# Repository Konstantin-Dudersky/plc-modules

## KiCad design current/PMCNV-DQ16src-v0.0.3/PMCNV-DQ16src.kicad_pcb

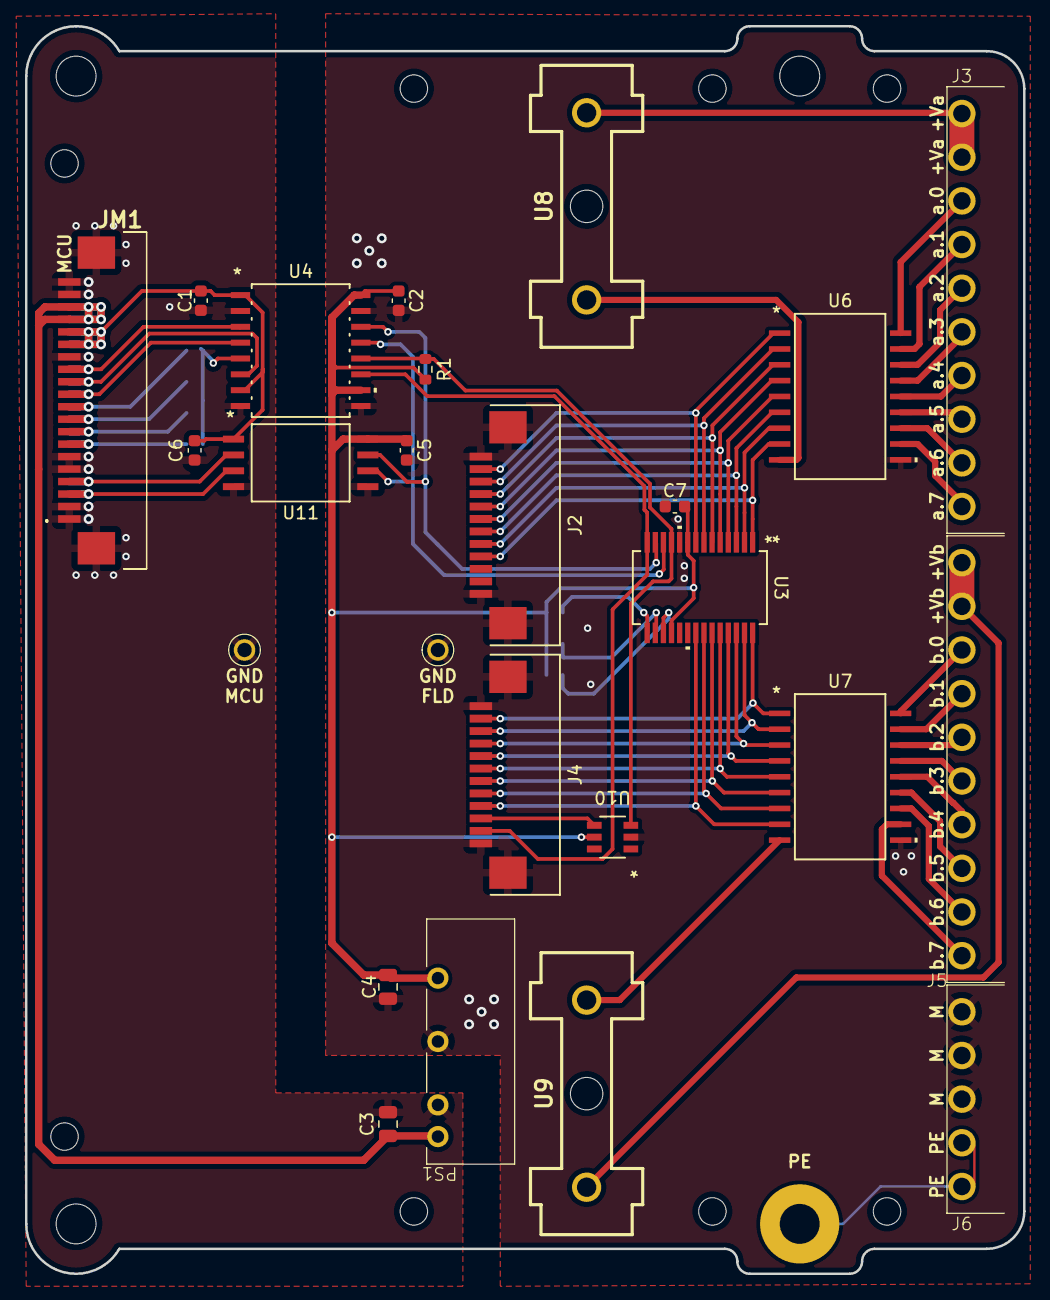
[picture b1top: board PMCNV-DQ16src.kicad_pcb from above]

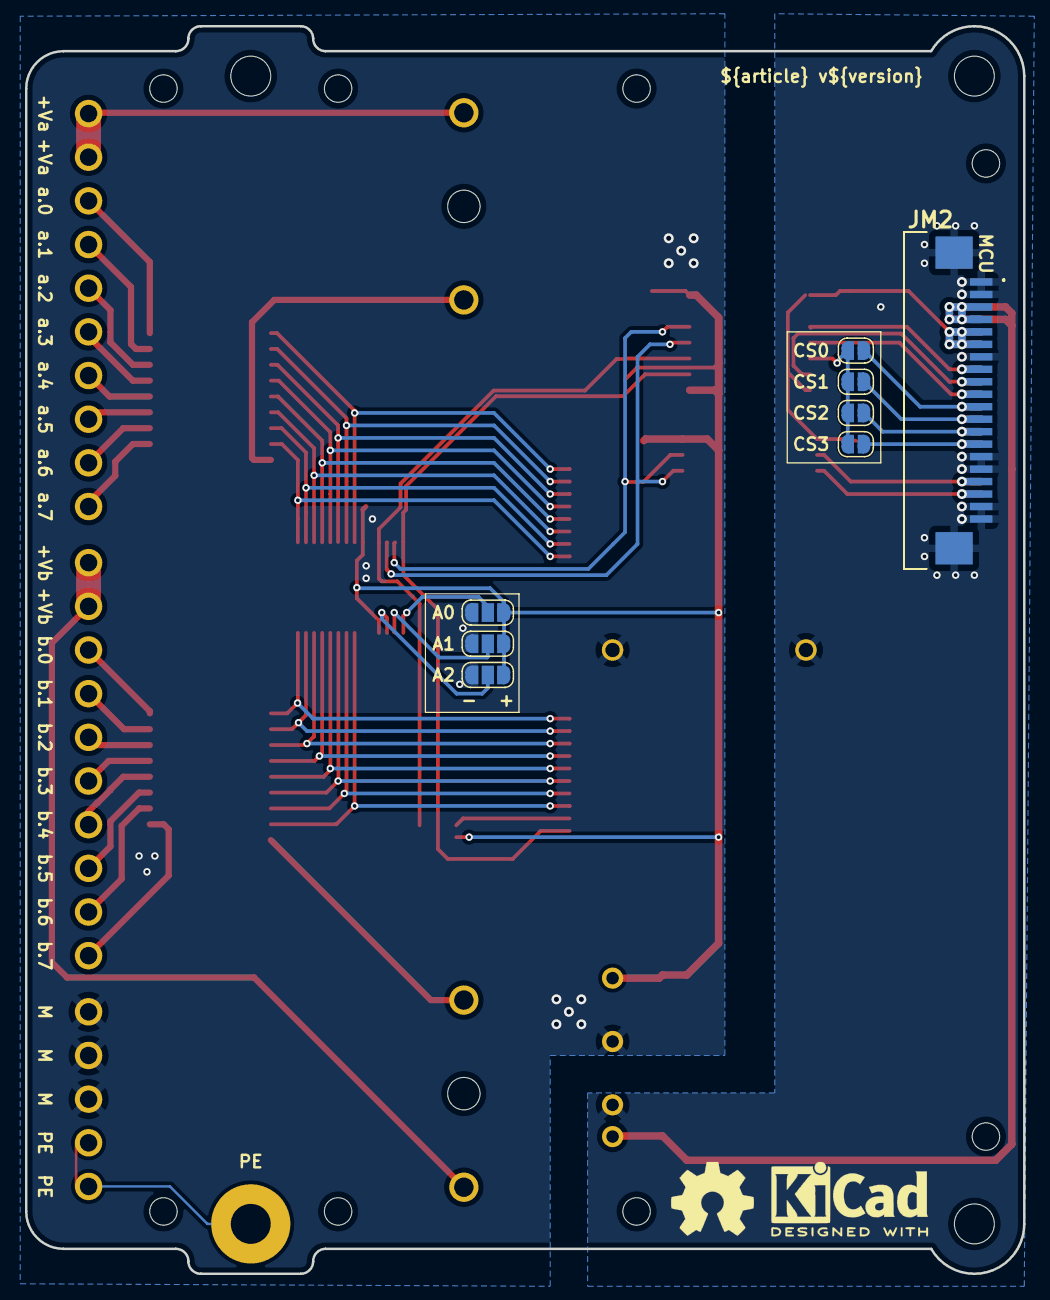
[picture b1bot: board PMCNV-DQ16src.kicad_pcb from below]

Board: 2 copper layers, 80.0 x 100.0 mm, 41 parts (10 on the bottom side), 60 nets.

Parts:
C1, C2, C5, C6, C7: 100nF; C_0603_1608Metric
C3: 4.7uF; C_0805_2012Metric
C4: 10uF; C_0805_2012Metric
H1, H2, H3: MountingHole_M3
J2, J4: AFA07-S12FCC-00; CONN10_AFA07-S12_JUS
J3, J5: 15EDGRC-3.5-10P
J6: 15EDGRC-3.5-05P
JM1, JM2: AFA07-S20FCC-00; AFA07S20FCA00
JP1, JP2, JP3, JP4: SolderJumper_2_Open; SolderJumper-2_P1.3mm_Open_RoundedPad1.0x1.5mm
JP5, JP6, JP7: SolderJumper_3_Open; SolderJumper-3_P1.3mm_Open_RoundedPad1.0x1.5mm
PE1: PE
PS1: 5V/5V; B2405LS-1WR3
R1: 10k; R_0603_1608Metric
SP1: PM_LED-xx-v0.0.1
U1: PM-ESP32C3_v0.0.5
U2, U5: 5117
U3: MCP23017_SS; SSOP28_MC_MCH
U4: CA-IS3741HW; SOIC16-WBW_CLG
U6, U7: TBD62783AFG; SOP18-P-375-1p27_TOS-M
U8, U9: 64900001039; 649-Series-Holder
U10: SN74LVC2G14DBVR; DBV6-M
U11: CA-IS3021G; SOICW8_CLG
kicad_logo: KiCad-Logo2_5mm_SilkScreen
oshw_logo: OSHW-Symbol_6.7x6mm_SilkScreen

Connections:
+3.3V_MCU: C1.1, C6.1, JM1.15 (Pin_11), JM1.16 (Pin_11), JM2.5, JM2.6, U4.1 (VDD), U4.7 (ENA), U11.1 (VDDa)
+5V_CNV: C2.1, C4.1, C5.1, C7.1, JP5.3 (B), JP6.3 (B), JP7.3 (B), PS1.6 (+V), R1.1, U3.9 (VDD), U3.18 (~RESET), U4.10 (ENB), U4.16 (VISO), U10.5 (VCC), U11.8 (VDDb)
+5V_MCU: C3.1, JM1.17 (Pin_11), JM1.18 (Pin_11), JM2.3, JM2.4, PS1.1 (Vin)
+V_a: J3.9, J3.10, U8.2
+V_b: J5.9, J5.10, U9.2
/A0: JP5.2 (C), U3.15 (A0)
/A1: JP6.2 (C), U3.16 (A1)
/A2: JP7.2 (C), U3.17 (A2)
/CS0_MCU: JM1.10, JM2.11, JP1.1 (A)
/CS1_MCU: JM1.9, JM2.12 (Pin_11), JP2.1 (A)
/CS2_MCU: JM1.8, JM2.13 (Pin_11), JP3.1 (A)
/CS3_MCU: JM1.7, JM2.14 (Pin_11), JP4.1 (A)
/CS_CNV: R1.2, U3.11 (~CS), U4.12 (VO3), U10.3 (2A)
/CS_LED: J4.3, U10.4 (2Y)
/CS_MCU: JP1.2 (B), JP2.2 (B), JP3.2 (B), JP4.2 (B), U4.5 (VI3)
/MISO_CNV: J4.2, U3.14 (SO), U4.11 (VI4)
/MISO_MCU: JM1.12 (Pin_11), JM2.9, U4.6 (VO4)
/MOSI_CNV: U3.13 (SI), U4.14 (VO1), U11.7 (SDAb)
/MOSI_MCU: JM1.13 (Pin_11), JM2.8, U4.3 (VI1)
/PE: J6.1, J6.2, PE1.1
/SCK_CNV: U3.12 (SCK), U4.13 (VO2), U11.6 (SCLb)
/SCK_MCU: JM1.11, JM2.10, U4.4 (VI2)
/SCL_MCU: JM1.3, JM2.18 (Pin_11), U11.3 (SCLa)
/SDA_MCU: JM1.4, JM2.17 (Pin_11), U11.2 (SDAa)
/a.0_in: J2.11, U3.8 (GPB7), U6.1 (I1)
/a.0_out: J3.8, U6.18 (O1)
/a.1_in: J2.10, U3.7 (GPB6), U6.2 (I2)
/a.1_out: J3.7, U6.17 (O2)
/a.2_in: J2.9, U3.6 (GPB5), U6.3 (I3)
/a.2_out: J3.6, U6.16 (O3)
/a.3_in: J2.8, U3.5 (GPB4), U6.4 (I4)
/a.3_out: J3.5, U6.15 (O4)
/a.4_in: J2.7, U3.4 (GPB3), U6.5 (I5)
/a.4_out: J3.4, U6.14 (O5)
/a.5_in: J2.6, U3.3 (GPB2), U6.6 (I6)
/a.5_out: J3.3, U6.13 (O6)
/a.6_in: J2.5, U3.2 (GPB1), U6.7 (I7)
/a.6_out: J3.2, U6.12 (O7)
/a.7_in: J2.4, U3.1 (GPB0), U6.8 (I8)
/a.7_out: J3.1, U6.11 (O8)
/b.0_in: J4.11, U3.28 (GPA7), U7.1 (I1)
/b.0_out: J5.8, U7.18 (O1)
/b.1_in: J4.10, U3.27 (GPA6), U7.2 (I2)
/b.1_out: J5.7, U7.17 (O2)
/b.2_in: J4.9, U3.26 (GPA5), U7.3 (I3)
/b.2_out: J5.6, U7.16 (O3)
/b.3_in: J4.8, U3.25 (GPA4), U7.4 (I4)
/b.3_out: J5.5, U7.15 (O4)
/b.4_in: J4.7, U3.24 (GPA3), U7.5 (I5)
/b.4_out: J5.4, U7.14 (O5)
/b.5_in: J4.6, U3.23 (GPA2), U7.6 (I6)
/b.5_out: J5.3, U7.13 (O6)
/b.6_in: J4.5, U3.22 (GPA1), U7.7 (I7)
/b.6_out: J5.2, U7.12 (O7)
/b.7_in: J4.4, U3.21 (GPA0), U7.8 (I8)
/b.7_out: J5.1, U7.11 (O8)
GND_CNV: C2.2, C4.2, C5.2, C7.2, J2.1, J2.12 (Pin_11), J2.13 (Pin_11), J4.1, J4.12 (Pin_11), J4.13 (Pin_11), J6.3, J6.4, J6.5, JP5.1 (A), JP6.1 (A), JP7.1 (A), PS1.4 (0V), U3.10 (VSS), U4.9 (GNDB), U4.15 (GNDB), U5.1, U6.10 (GND), U7.10 (GND), U10.2 (GND), U11.5 (GNDb)
GND_MCU: C1.2, C3.2, C6.2, JM1.1, JM1.2, JM1.5, JM1.6, JM1.14 (Pin_11), JM1.19 (Pin_11), JM1.20 (Pin_11), JM1.MP1 (Pin_11), JM1.MP2 (Pin_11), JM2.1, JM2.2, JM2.7, JM2.15 (Pin_11), JM2.16 (Pin_11), JM2.19 (Pin_11), JM2.20 (Pin_11), JM2.MP1 (Pin_11), JM2.MP2 (Pin_11), PS1.2 (GND), U2.1, U4.2 (GNDA), U4.8 (GNDA), U11.4 (GNDa)
unnamed: U6.9 (VCC), U8.1
unnamed: U7.9 (VCC), U9.1

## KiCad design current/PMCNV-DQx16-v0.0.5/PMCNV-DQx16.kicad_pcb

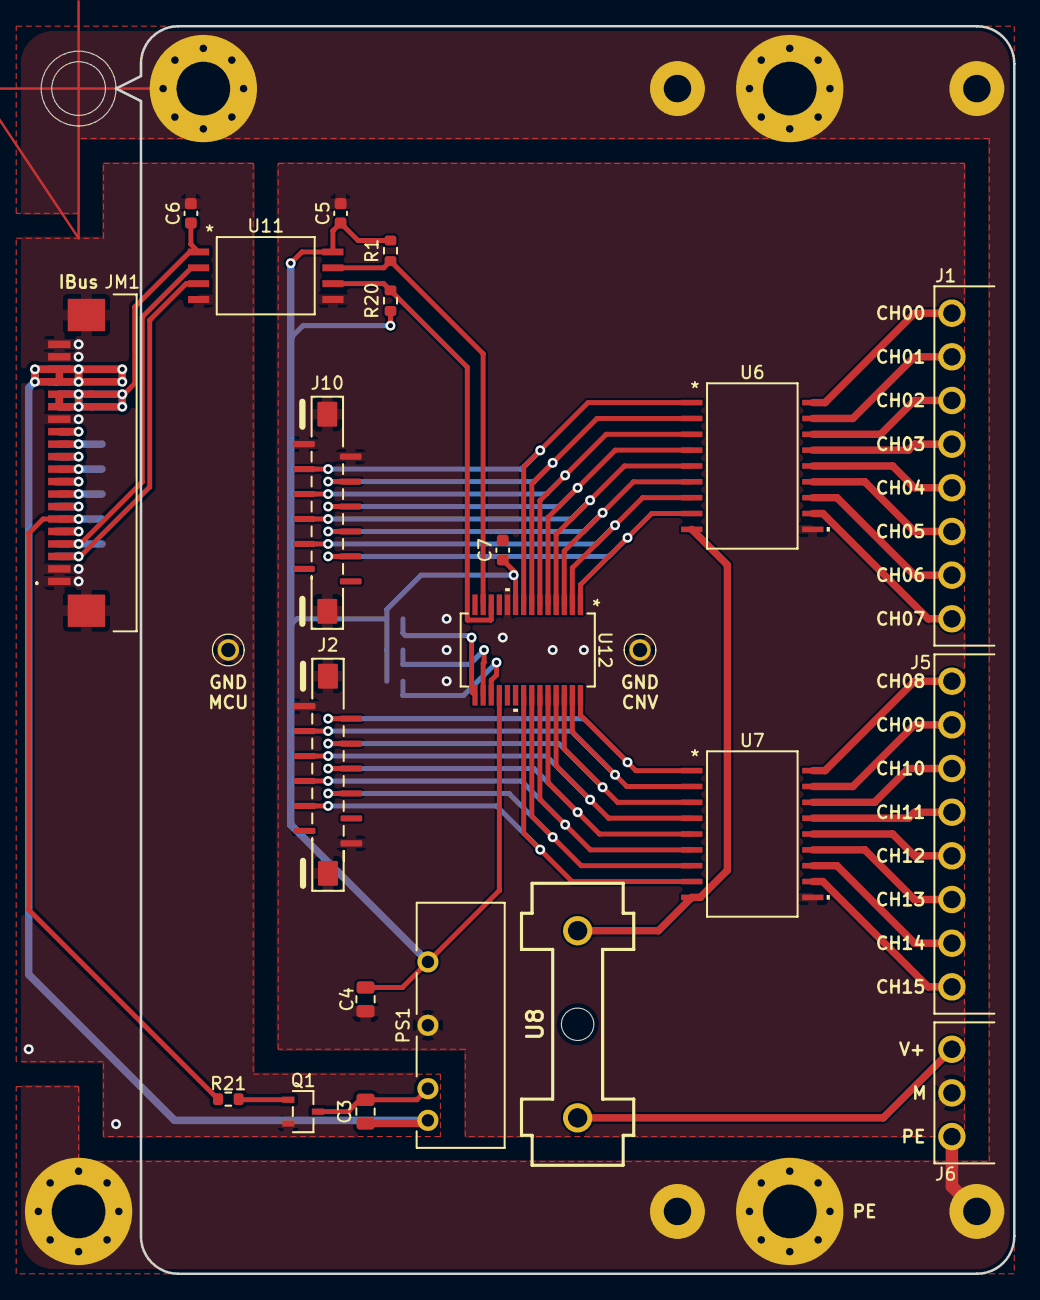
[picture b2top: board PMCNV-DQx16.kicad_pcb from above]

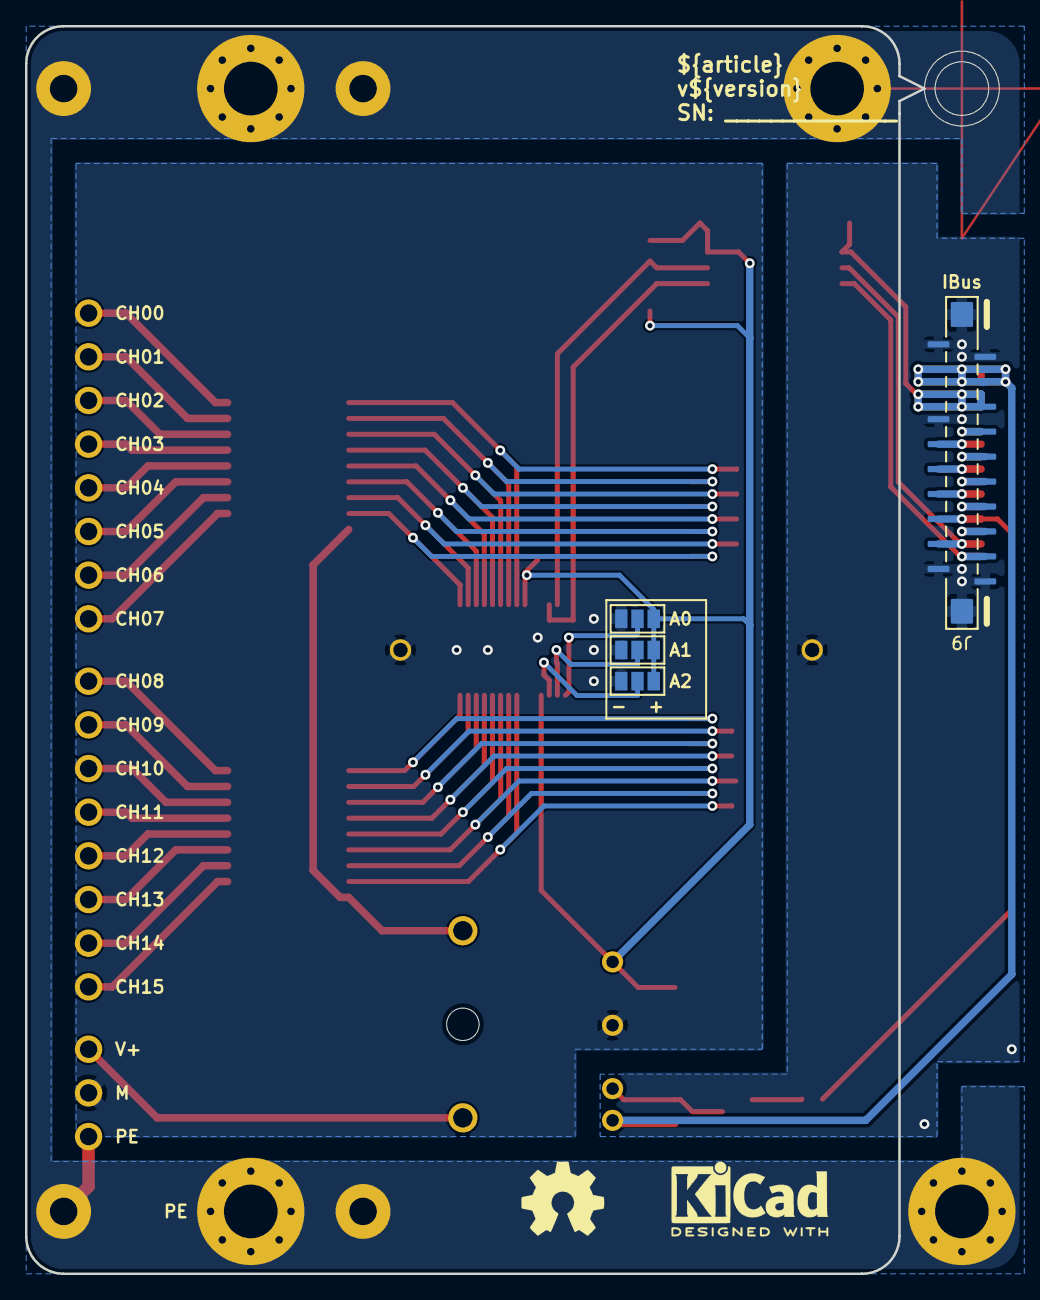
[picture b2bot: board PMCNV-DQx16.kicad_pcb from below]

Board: 2 copper layers, 78.0 x 100.0 mm, 34 parts (6 on the bottom side), 58 nets.

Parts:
C3: 4.7uF; C_0805_2012Metric
C4: 10uF; C_0805_2012Metric
C5, C6, C7: 100nF; C_0603_1608Metric
H1, H2, H3, H4: M4; MountingHole_4.3mm_M4_Pad_Via
J1, J5: 15EDGRC-3.5-08P
J2, J10: AFA11-S12GLA-00
J6: 15EDGRC-3.5-03P
J9: AFA11-S20GLA-00
JM1: AFA07-S20FCC-00; AFA07S20FCA00
JP5, JP6, JP7: SolderJumper_3_Open; SolderJumper-3_P1.3mm_Open_Pad1.0x1.5mm
PS1: 5V/5V; B2405LS-1WR3
Q1: 2N7002K; 2N7002K_ONS
R1, R20: 3k3; R_0603_1608Metric
R21: 100R; R_0603_1608Metric
SP1: PMLED-xx-v0.0.2
U2, U5: 5117
U6, U7: TBD62783AFG; SOP18-P-375-1p27_TOS-M
U8: 64900001039; 649-Series-Holder
U11: CA-IS3021G; SOICW8_CLG
U12: MCP23017_SS; SSOP28_MC_MCH
kicad_logo: KiCad-Logo2_5mm_SilkScreen
oshw_logo: OSHW-Symbol_6.7x6mm_SilkScreen

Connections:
+3.3V_MCU: C6.1, J9.15 (Pin_11), J9.16 (Pin_11), JM1.15 (Pin_11), JM1.16 (Pin_11), U11.1 (VDDa)
+5V_CNV: C4.1, C5.1, C7.1, JP5.3 (B), JP6.3 (B), JP7.3 (B), PS1.6 (+V), R1.1, R20.1, U11.8 (VDDb), U12.9 (VDD), U12.18 (~RESET)
+5V_MCU: C3.1, J9.17 (Pin_11), J9.18 (Pin_11), JM1.17 (Pin_11), JM1.18 (Pin_11), PS1.1 (Vin)
+V: U6.9 (VCC), U7.9 (VCC), U8.2
/A0: JP5.2 (C), U12.15 (A0)
/A1: JP6.2 (C), U12.16 (A1)
/A2: JP7.2 (C), U12.17 (A2)
/CH00_in: J10.3, U6.1 (I1), U12.8 (GPB7)
/CH01_in: J10.4, U6.2 (I2), U12.7 (GPB6)
/CH02_in: J10.5, U6.3 (I3), U12.6 (GPB5)
/CH03_in: J10.6, U6.4 (I4), U12.5 (GPB4)
/CH04_in: J10.7, U6.5 (I5), U12.4 (GPB3)
/CH05_in: J10.8, U6.6 (I6), U12.3 (GPB2)
/CH06_in: J10.9, U6.7 (I7), U12.2 (GPB1)
/CH07_in: J10.10, U6.8 (I8), U12.1 (GPB0)
/CH08_in: J2.2, U7.1 (I1), U12.28 (GPA7)
/CH09_in: J2.3, U7.2 (I2), U12.27 (GPA6)
/CH10_in: J2.4, U7.3 (I3), U12.26 (GPA5)
/CH11_in: J2.5, U7.4 (I4), U12.25 (GPA4)
/CH12_in: J2.6, U7.5 (I5), U12.24 (GPA3)
/CH13_in: J2.7, U7.6 (I6), U12.23 (GPA2)
/CH14_in: J2.8, U7.7 (I7), U12.22 (GPA1)
/CH15_in: J2.9, U7.8 (I8), U12.21 (GPA0)
/CS0_MCU: J9.10, JM1.10
/CS1_MCU: J9.9, JM1.9
/CS2_MCU: J9.8, JM1.8
/CS3_MCU: J9.7, JM1.7
/MISO_MCU: J9.12 (Pin_11), JM1.12 (Pin_11)
/MOSI_MCU: J9.13 (Pin_11), JM1.13 (Pin_11)
/RST: J9.6, JM1.6, R21.1
/SCK_MCU: J9.11, JM1.11
/SCL_CNV: R20.2, U11.6 (SCLb), U12.12 (SCK)
/SCL_MCU: J9.3, JM1.3, U11.3 (SCLa)
/SDA_CNV: R1.2, U11.7 (SDAb), U12.13 (SI)
/SDA_MCU: J9.4, JM1.4, U11.2 (SDAa)
/a.0_out: J1.8, U6.18 (O1)
/a.1_out: J1.7, U6.17 (O2)
/a.2_out: J1.6, U6.16 (O3)
/a.3_out: J1.5, U6.15 (O4)
/a.4_out: J1.4, U6.14 (O5)
/a.5_out: J1.3, U6.13 (O6)
/a.6_out: J1.2, U6.12 (O7)
/a.7_out: J1.1, U6.11 (O8)
/b.0_out: J5.8, U7.18 (O1)
/b.1_out: J5.7, U7.17 (O2)
/b.2_out: J5.6, U7.16 (O3)
/b.3_out: J5.5, U7.15 (O4)
/b.4_out: J5.4, U7.14 (O5)
/b.5_out: J5.3, U7.13 (O6)
/b.6_out: J5.2, U7.12 (O7)
/b.7_out: J5.1, U7.11 (O8)
GND_CNV: C4.2, C5.2, C7.2, J2.1, J2.12 (Pin_11), J2.MP1 (Pin_11), J2.MP2 (Pin_11), J6.2, J10.1, J10.2, J10.MP1 (Pin_11), J10.MP2 (Pin_11), JP5.1 (A), JP6.1 (A), JP7.1 (A), PS1.4 (0V), U5.1, U6.10 (GND), U7.10 (GND), U11.5 (GNDb), U12.10 (VSS)
GND_MCU: C6.2, J9.1, J9.2, J9.14 (Pin_11), J9.19 (Pin_11), J9.20 (Pin_11), J9.MP1 (Pin_11), J9.MP2 (Pin_11), JM1.1, JM1.2, JM1.14 (Pin_11), JM1.19 (Pin_11), JM1.20 (Pin_11), JM1.MP1 (Pin_11), JM1.MP2 (Pin_11), Q1.2 (S), U2.1, U11.4 (GNDa)
unnamed: J6.3, U8.1
unnamed: J9.5, JM1.5
unnamed: C3.2, PS1.2 (GND), Q1.3 (D)
unnamed: Q1.1 (G), R21.2
PE: H1.1 (1_1), H2.1 (1_1), H3.1 (1_1), H4.1 (1_1), J6.1, SP1.PE (PE_PE)

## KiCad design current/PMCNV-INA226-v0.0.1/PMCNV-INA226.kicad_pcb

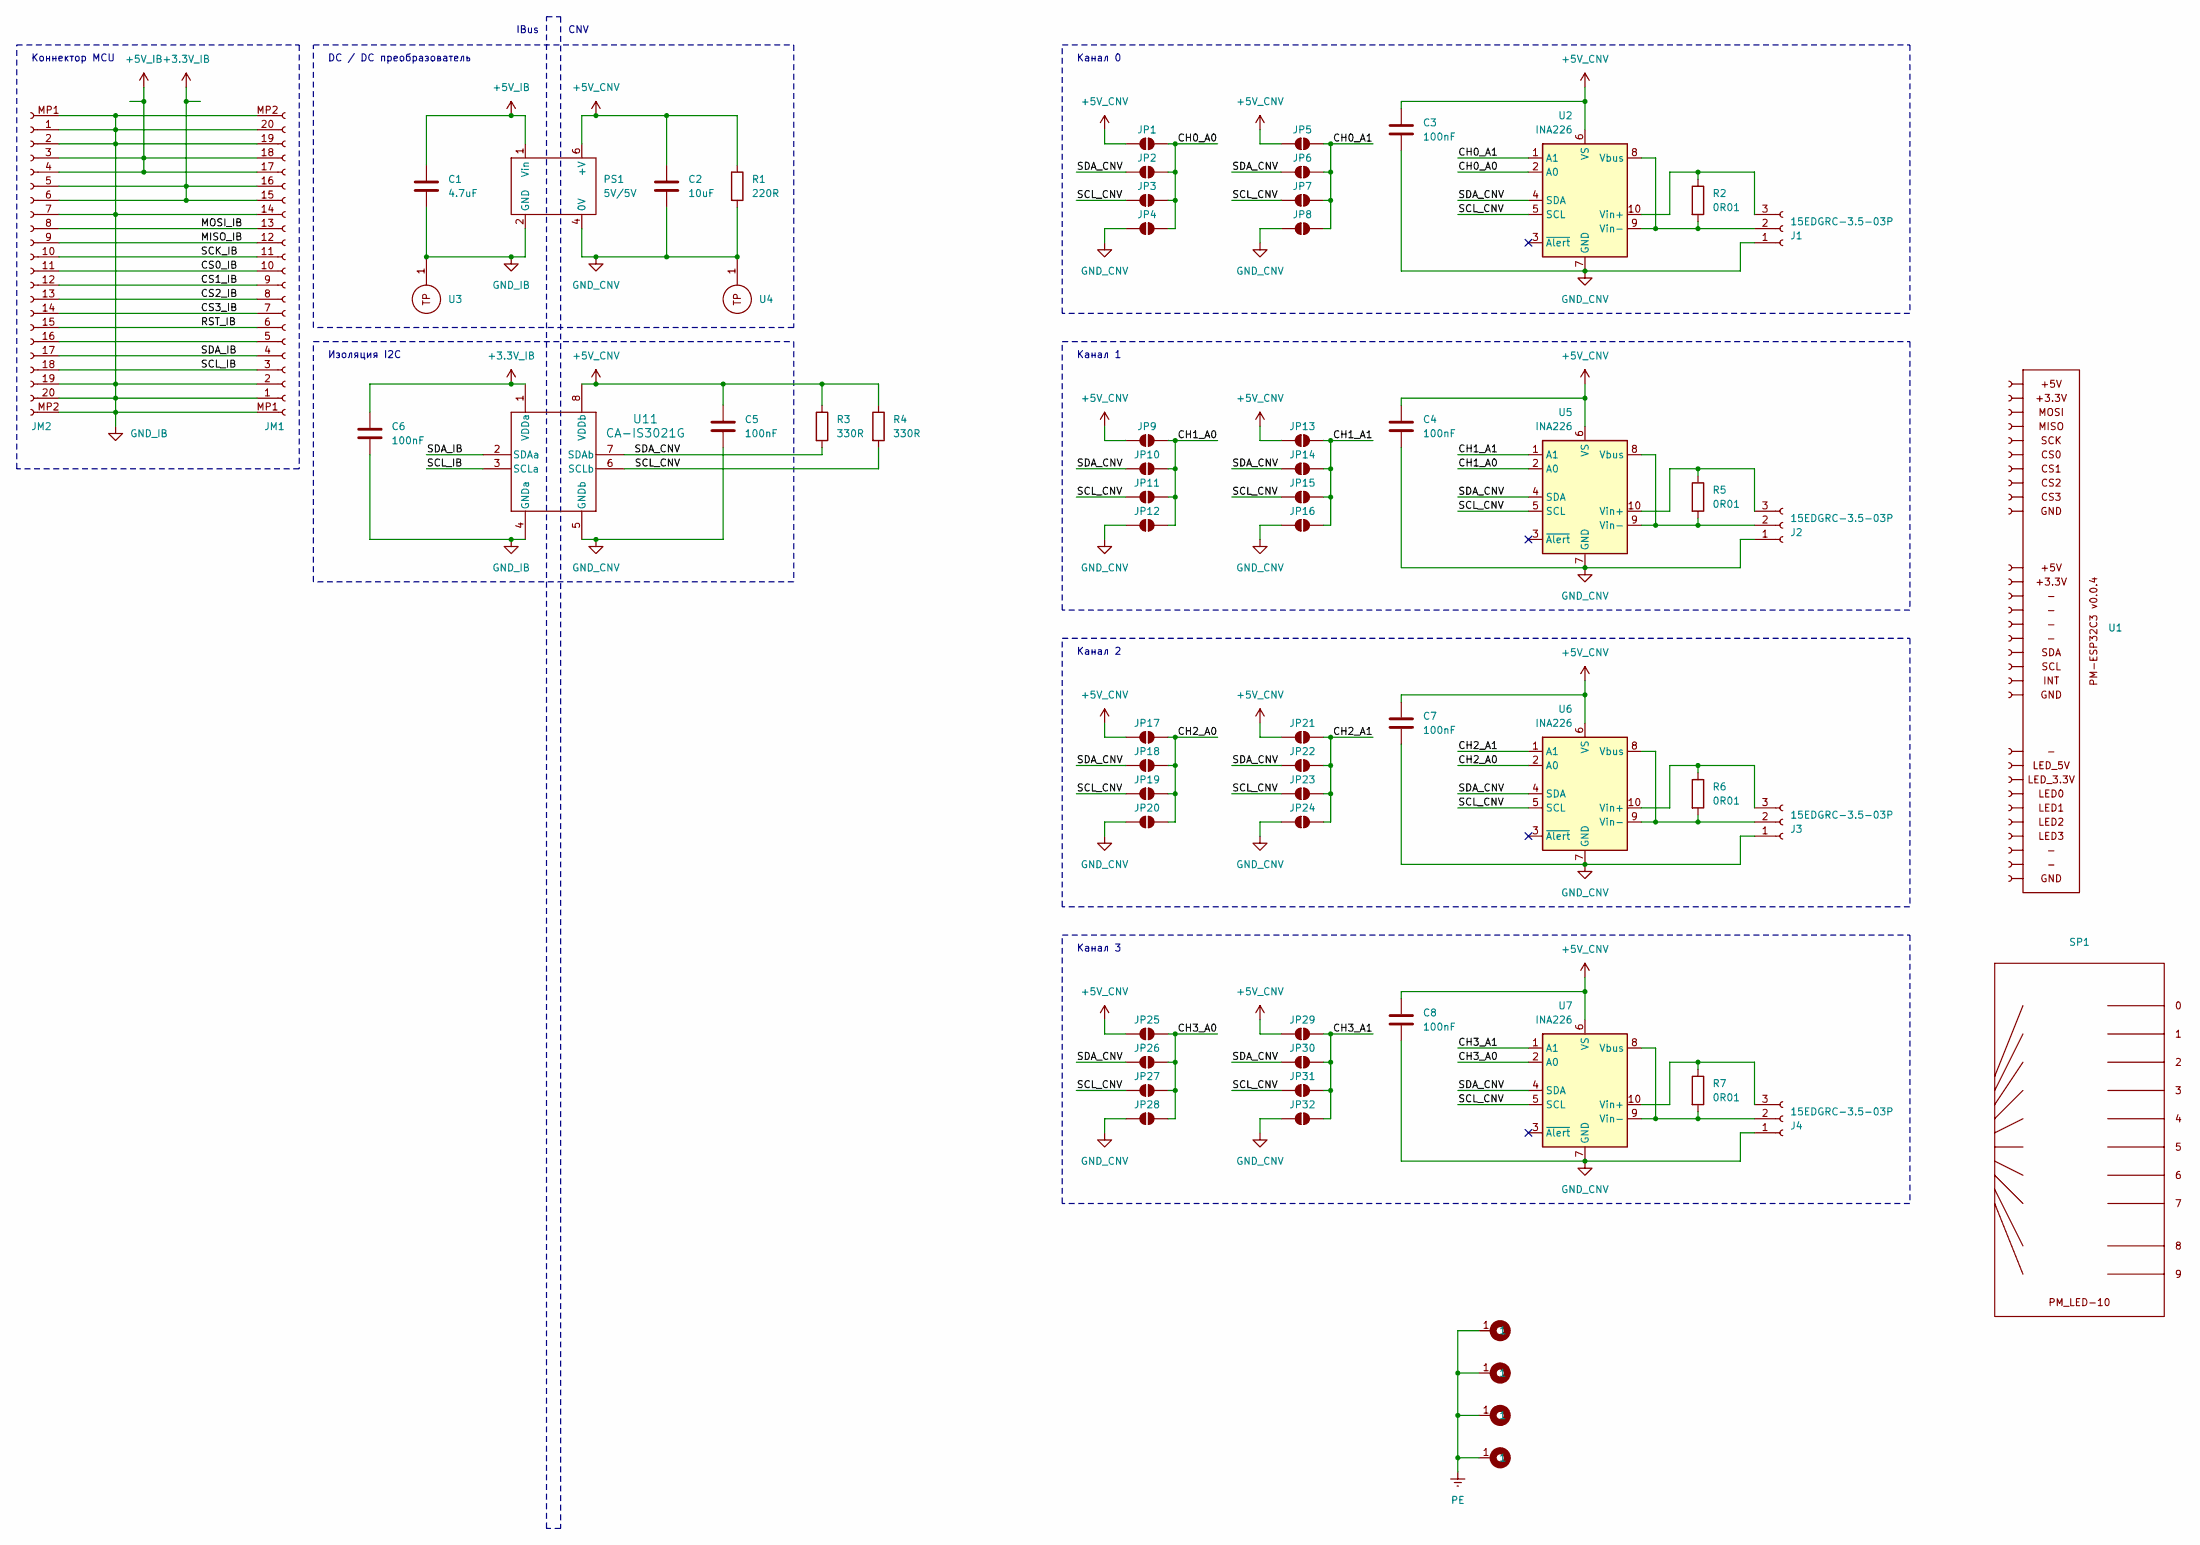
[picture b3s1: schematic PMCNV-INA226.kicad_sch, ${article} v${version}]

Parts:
C1: 4.7uF; C_0805_2012Metric; part_ipn C_4.7uF_16V_0805_MLCC-X7R
C2: 10uF; C_0805_2012Metric; part_ipn C_10uF_16V_0805_MLCC-X7R
C3, C4, C5, C6, C7, C8: 100nF; C_0603_1608Metric; part_ipn C_100nF_16V_0603_MLCC-X7R
H1, H2, H3, H4: M4; MountingHole_4.3mm_M4_Pad_Via
J1, J2, J3, J4: 15EDGRC-3.5-03P; part_ipn 15EDGRC-3.5-03P
JM1, JM2: AFA07-S20FCC-00; AFA07S20FCA00; part_ipn AFA07-S20FCC-00
JP1, JP2, JP3, JP4, JP5, JP6, JP7, JP8, JP9, JP10, JP11, JP12, JP13, JP14, JP15, JP16, JP17, JP18, JP19, JP20, JP21, JP22, JP23, JP24, JP25, JP26, JP27, JP28, JP29, JP30, JP31, JP32: SolderJumper_2_Open; SolderJumper-2_P1.3mm_Open_RoundedPad1.0x1.5mm
PS1: 5V/5V; B2405LS-1WR3; part_ipn B0505LS-1W
R1: 220R; R_0603_1608Metric; part_ipn R_220R_0603_1%
R2, R5, R6, R7: 0R01; R_2512_6332Metric; part_ipn R_0R01_2512_1%_50ppm
R3, R4: 330R; R_0603_1608Metric; part_ipn R_330R_0603_1%
SP1: PM_LED-xx-v0.0.1; part_ipn PM_LED-10-v0.0.1
U1: PM-ESP32C3_v0.0.5; part_ipn PM-ESP32C3_v0.0.4
U2, U5, U6, U7: INA226; VSSOP-10_3x3mm_P0.5mm
U3, U4: 5117; part_ipn Keystone_5117
U11: CA-IS3021G; SOICW8_CLG; part_ipn CA-IS3021G

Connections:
+3.3V_IB: C6.1, JM1.15 (Pin_11), JM1.16 (Pin_11), JM2.5, JM2.6, U11.1 (VDDa)
+5V_CNV: C2.1, C3.1, C4.1, C5.1, C7.1, C8.1, JP1.1 (A), JP5.1 (A), JP9.1 (A), JP13.1 (A), JP17.1 (A), JP21.1 (A), JP25.1 (A), JP29.1 (A), PS1.6 (+V), R1.1, R3.1, R4.1, U2.6 (VS), U5.6 (VS), U6.6 (VS), U7.6 (VS), U11.8 (VDDb)
+5V_IB: C1.1, JM1.17 (Pin_11), JM1.18 (Pin_11), JM2.3, JM2.4, PS1.1 (Vin)
/CH0_A0: JP1.2 (B), JP2.2 (B), JP3.2 (B), JP4.2 (B), U2.2 (A0)
/CH0_A1: JP5.2 (B), JP6.2 (B), JP7.2 (B), JP8.2 (B), U2.1 (A1)
/CH1_A0: JP9.2 (B), JP10.2 (B), JP11.2 (B), JP12.2 (B), U5.2 (A0)
/CH1_A1: JP13.2 (B), JP14.2 (B), JP15.2 (B), JP16.2 (B), U5.1 (A1)
/CH2_A0: JP17.2 (B), JP18.2 (B), JP19.2 (B), JP20.2 (B), U6.2 (A0)
/CH2_A1: JP21.2 (B), JP22.2 (B), JP23.2 (B), JP24.2 (B), U6.1 (A1)
/CH3_A0: JP25.2 (B), JP26.2 (B), JP27.2 (B), JP28.2 (B), U7.2 (A0)
/CH3_A1: JP29.2 (B), JP30.2 (B), JP31.2 (B), JP32.2 (B), U7.1 (A1)
/CS0_IB: JM1.10, JM2.11
/CS1_IB: JM1.9, JM2.12 (Pin_11)
/CS2_IB: JM1.8, JM2.13 (Pin_11)
/CS3_IB: JM1.7, JM2.14 (Pin_11)
/MISO_IB: JM1.12 (Pin_11), JM2.9
/MOSI_IB: JM1.13 (Pin_11), JM2.8
/RST_IB: JM1.6, JM2.15 (Pin_11)
/SCK_IB: JM1.11, JM2.10
/SCL_CNV: JP3.1 (A), JP7.1 (A), JP11.1 (A), JP15.1 (A), JP19.1 (A), JP23.1 (A), JP27.1 (A), JP31.1 (A), R4.2, U2.5 (SCL), U5.5 (SCL), U6.5 (SCL), U7.5 (SCL), U11.6 (SCLb)
/SCL_IB: JM1.3, JM2.18 (Pin_11), U11.3 (SCLa)
/SDA_CNV: JP2.1 (A), JP6.1 (A), JP10.1 (A), JP14.1 (A), JP18.1 (A), JP22.1 (A), JP26.1 (A), JP30.1 (A), R3.2, U2.4 (SDA), U5.4 (SDA), U6.4 (SDA), U7.4 (SDA), U11.7 (SDAb)
/SDA_IB: JM1.4, JM2.17 (Pin_11), U11.2 (SDAa)
GND_CNV: C2.2, C3.2, C4.2, C5.2, C7.2, C8.2, J1.1, J2.1, J3.1, J4.1, JP4.1 (A), JP8.1 (A), JP12.1 (A), JP16.1 (A), JP20.1 (A), JP24.1 (A), JP28.1 (A), JP32.1 (A), PS1.4 (0V), R1.2, U2.7 (GND), U4.1, U5.7 (GND), U6.7 (GND), U7.7 (GND), U11.5 (GNDb)
GND_IB: C1.2, C6.2, JM1.1, JM1.2, JM1.14 (Pin_11), JM1.19 (Pin_11), JM1.20 (Pin_11), JM1.MP1 (Pin_11), JM1.MP2 (Pin_11), JM2.1, JM2.2, JM2.7, JM2.19 (Pin_11), JM2.20 (Pin_11), JM2.MP1 (Pin_11), JM2.MP2 (Pin_11), PS1.2 (GND), U3.1, U11.4 (GNDa)
unnamed: J1.2, R2.2, U2.8 (Vbus), U2.9 (Vin-)
unnamed: J1.3, R2.1, U2.10 (Vin+)
unnamed: J2.2, R5.2, U5.8 (Vbus), U5.9 (Vin-)
unnamed: J2.3, R5.1, U5.10 (Vin+)
unnamed: J3.2, R6.2, U6.8 (Vbus), U6.9 (Vin-)
unnamed: J3.3, R6.1, U6.10 (Vin+)
unnamed: J4.2, R7.2, U7.8 (Vbus), U7.9 (Vin-)
unnamed: J4.3, R7.1, U7.10 (Vin+)
unnamed: JM1.5, JM2.16 (Pin_11)
PE: H1.1, H2.1, H3.1, H4.1

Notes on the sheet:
IBus
Канал 1
DC / DC преобразователь
Изоляция I2C
Канал 3
CNV
Канал 2
Канал 0
Коннектор MCU

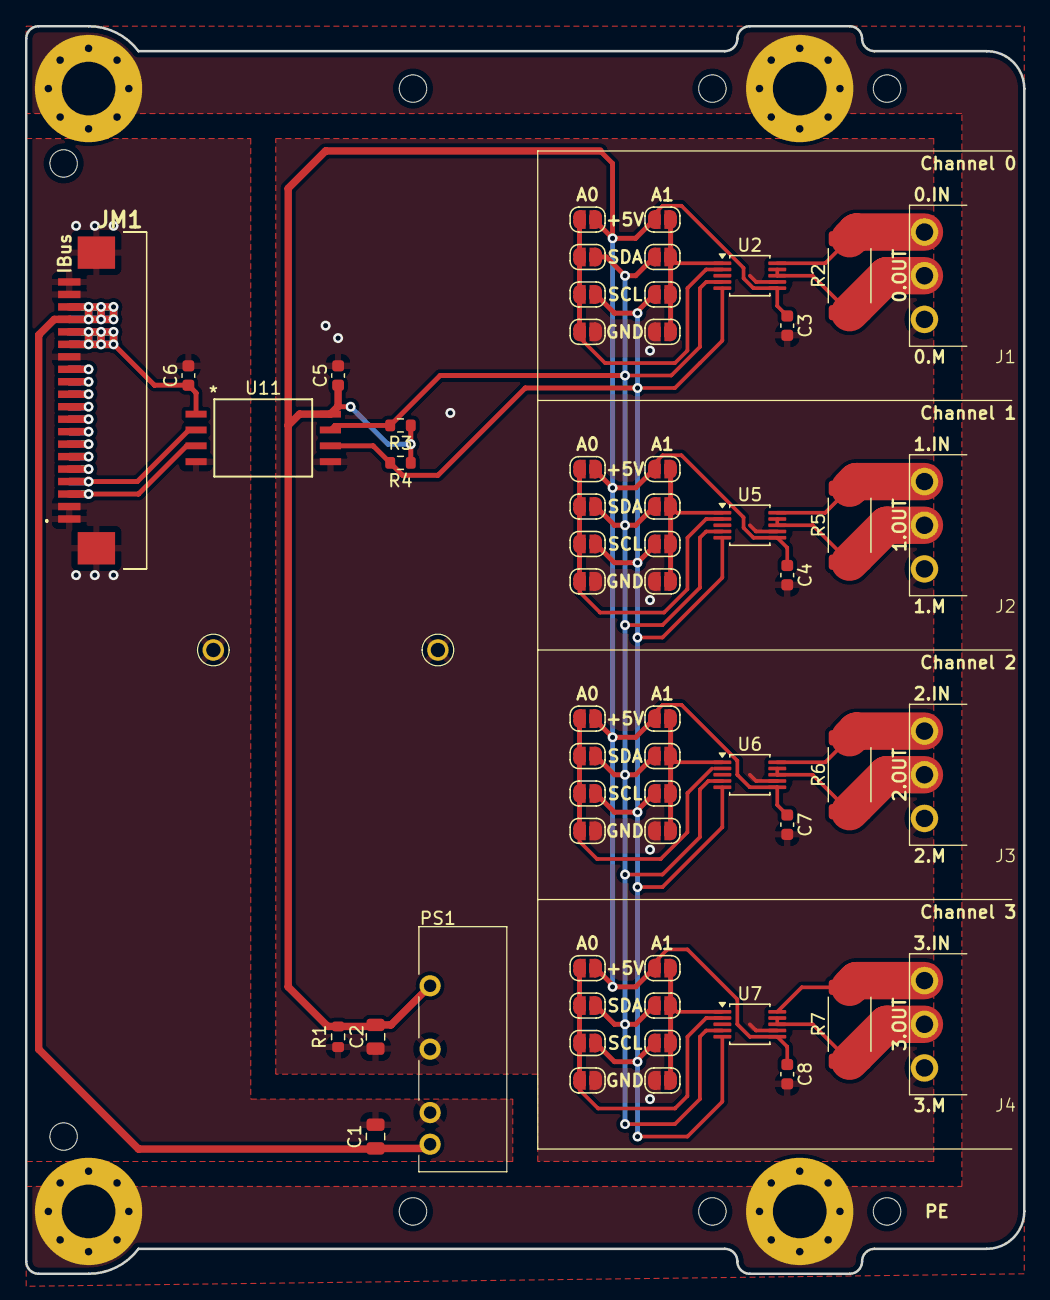
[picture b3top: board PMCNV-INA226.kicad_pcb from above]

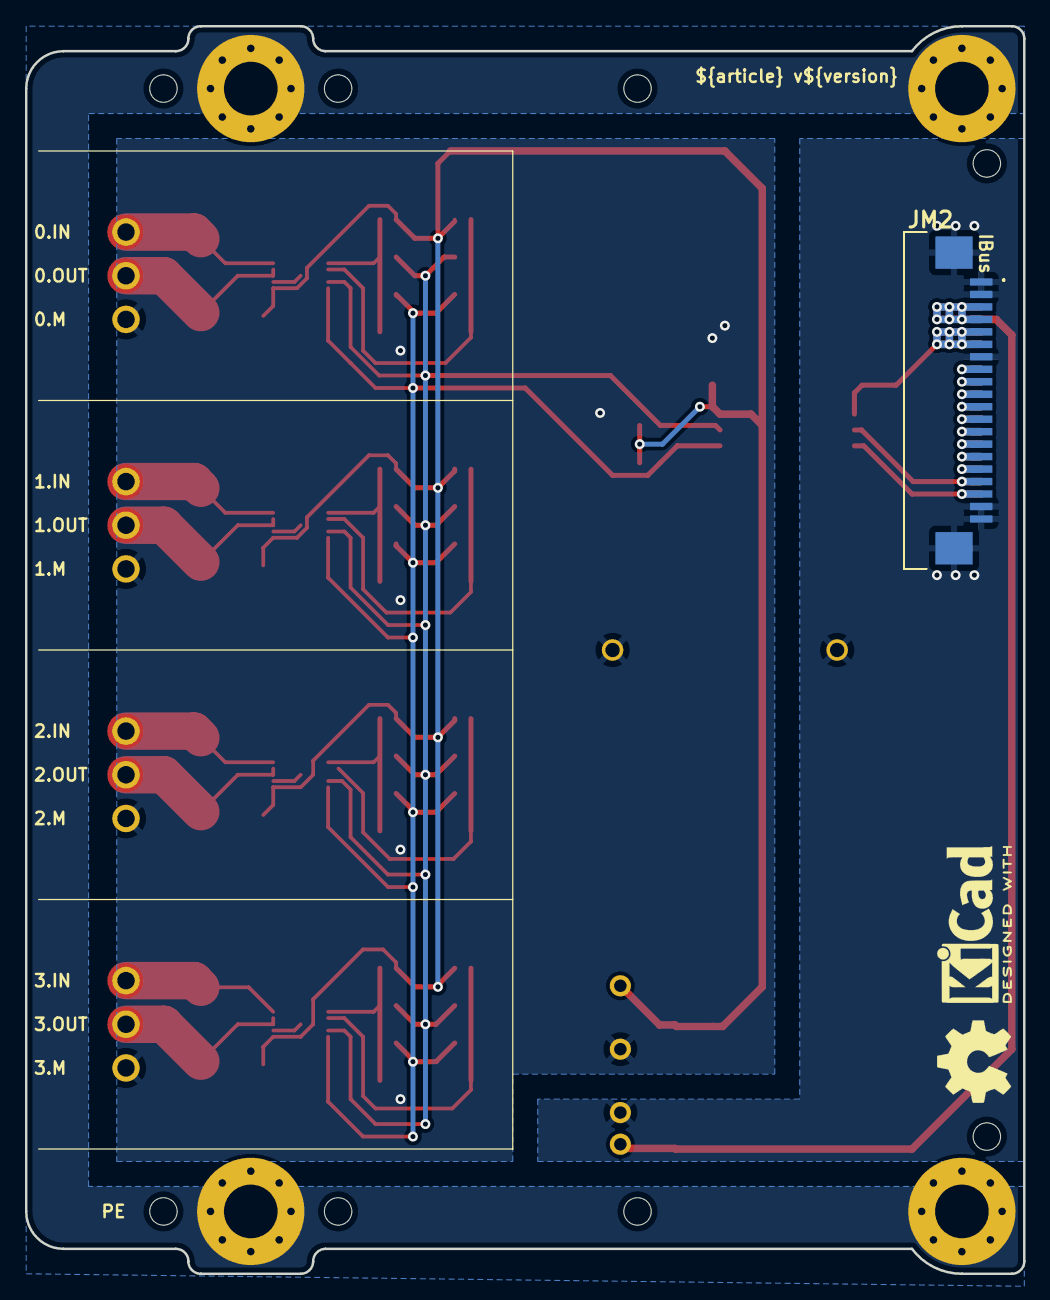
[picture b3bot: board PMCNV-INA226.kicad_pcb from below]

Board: 2 copper layers, 80.0 x 100.0 mm, 69 parts (3 on the bottom side), 35 nets.

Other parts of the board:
kicad_logo: KiCad-Logo2_5mm_SilkScreen
oshw_logo: OSHW-Symbol_6.7x6mm_SilkScreen

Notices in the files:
parts and their libraries:
COPYRIGHT: Copyright (C) 2023 Ultra Librarian. All rights reserved.
